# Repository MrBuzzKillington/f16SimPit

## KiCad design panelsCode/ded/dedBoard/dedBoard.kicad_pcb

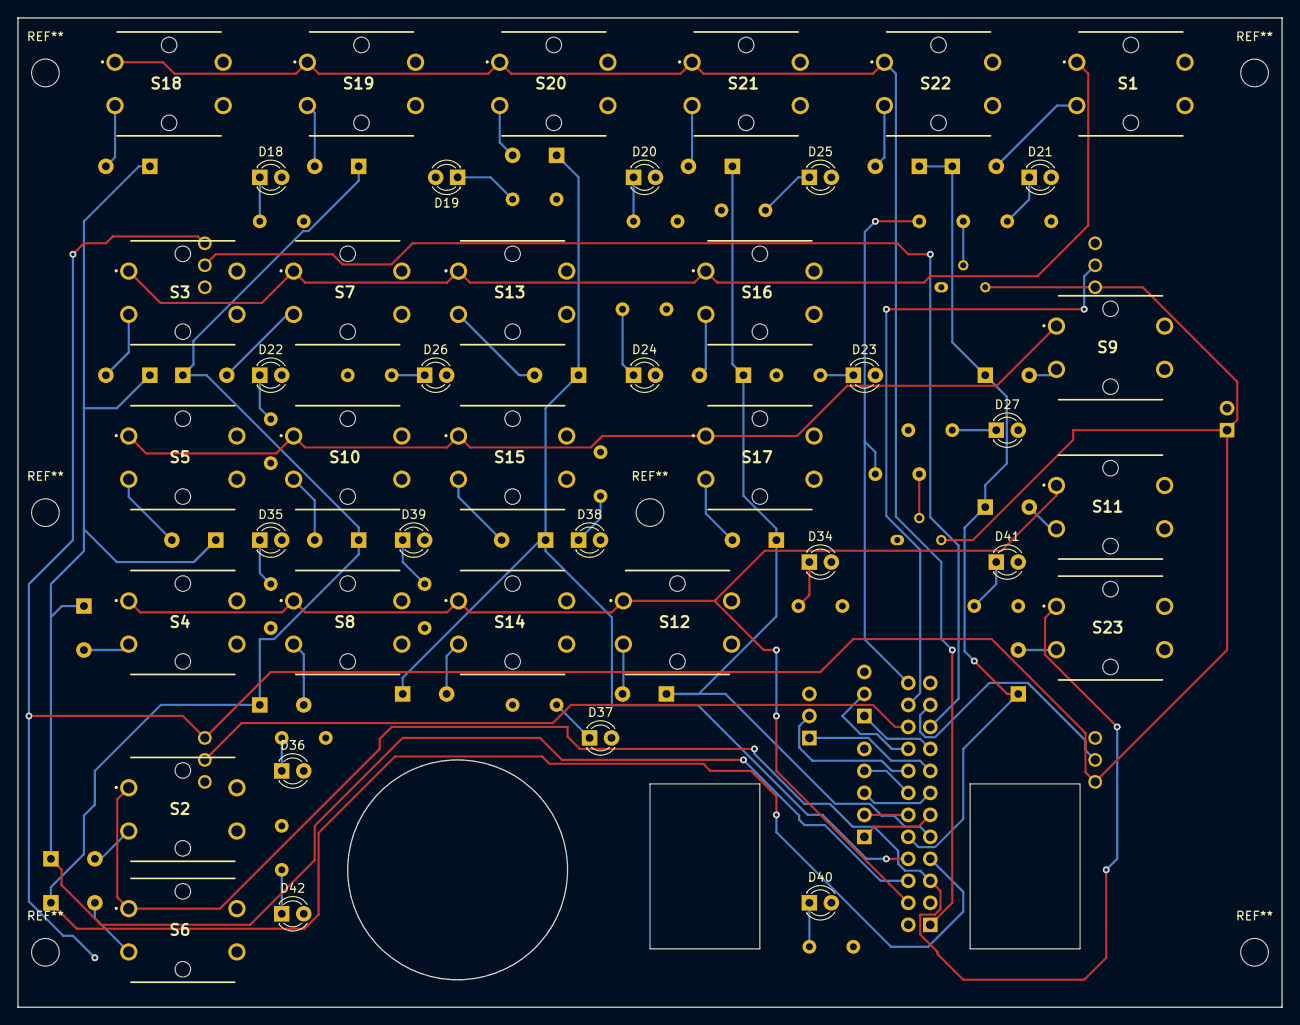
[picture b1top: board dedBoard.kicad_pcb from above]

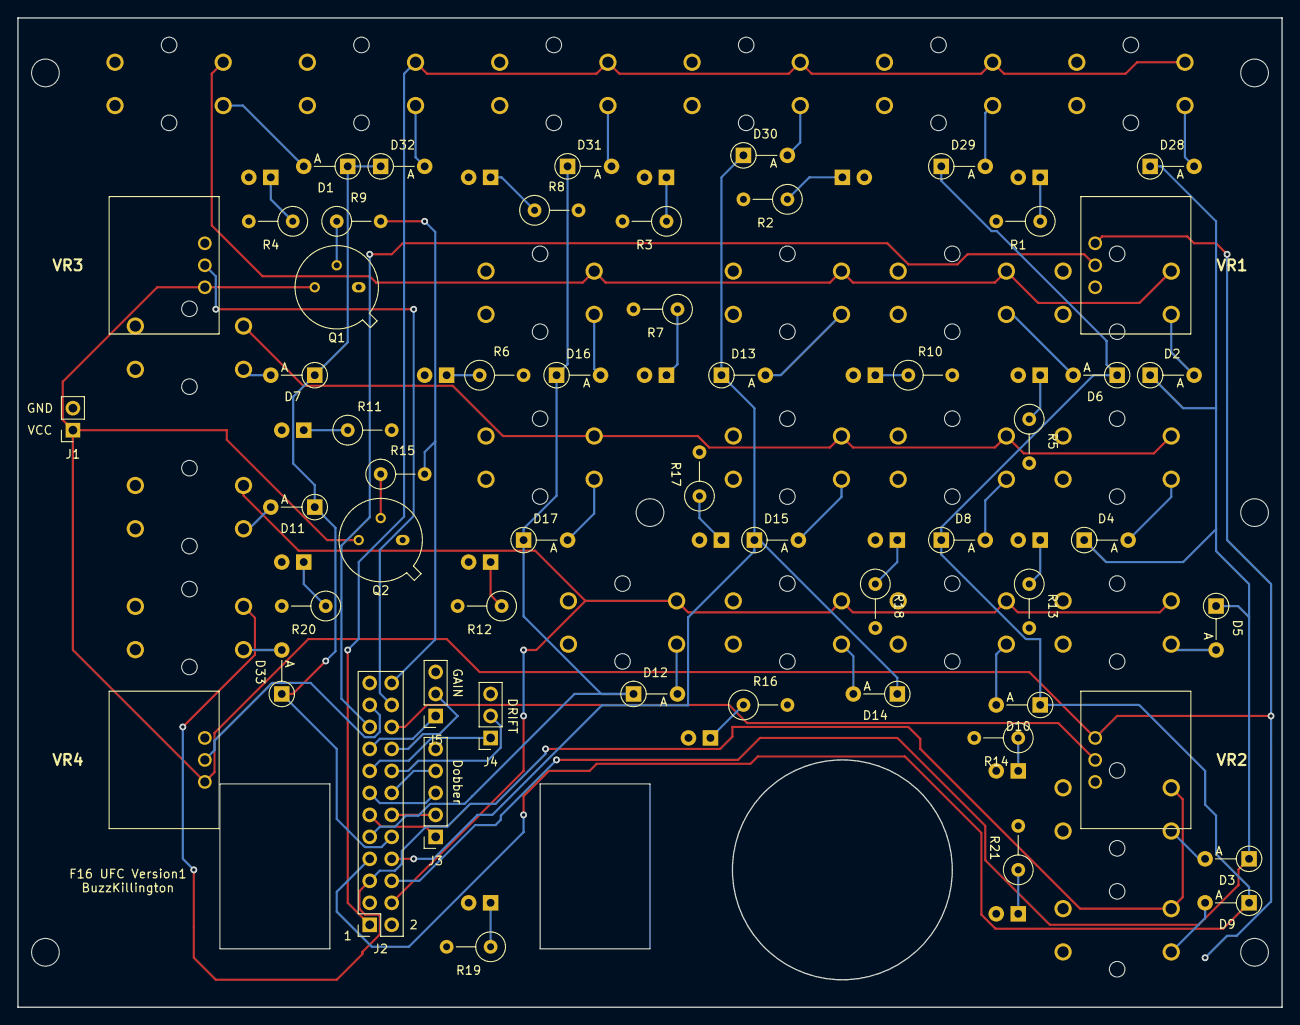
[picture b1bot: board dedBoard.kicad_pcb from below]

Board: 4 copper layers, 146.0 x 114.3 mm, 97 parts (55 on the bottom side), 71 nets.

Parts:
D1, D2, D3, D4, D5, D6, D7, D8, D9, D10, D11, D12, D13, D14, D15, D16, D17, D28, D29, D30, D31, D32, D33: D; D_A-405_P5.08mm_Vertical_AnodeUp
D18, D19, D20, D21, D22, D23, D24, D25, D26, D27, D34, D35, D36, D37, D38, D39, D40, D41, D42: LED; LED_D3.0mm
J1: Conn_01x02; PinSocket_1x02_P2.54mm_Vertical
J2: Conn_02x12_Odd_Even; PinSocket_2x12_P2.54mm_Vertical
J3: Conn_01x05; PinSocket_1x05_P2.54mm_Vertical
J4, J5: Conn_01x03; PinSocket_1x03_P2.54mm_Vertical
Q1, Q2: 2N2219; TO-39-3
R1, R2, R3, R4, R5, R6, R7, R8, R10, R11, R12, R13, R14, R16, R17, R18, R19, R20, R21: 520; R_Axial_DIN0309_L9.0mm_D3.2mm_P5.08mm_Vertical
R9, R15: 1000; R_Axial_DIN0309_L9.0mm_D3.2mm_P5.08mm_Vertical
S1, S2, S3, S4, S5, S6, S7, S8, S9, S10, S11, S12, S13, S14, S15, S16, S17, S18, S19, S20, S21, S22, S23: SKHCBEA010
VR1, VR2, VR3, VR4: 91A1A-B28-B13L; 91A1AB28B13L

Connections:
/LED1: D18.2, D19.2, D20.2, D21.2, D22.2, D23.2, D24.2, D25.2, D26.2, D27.2, Q1.1
/LED2: D34.2, D35.2, D36.2, D37.2, D38.2, D39.2, D40.2, D41.2, D42.2, Q2.1
COL1: D2.1, D3.1, D4.1, D5.1, D28.1, J2.6
COL2: D6.1, D8.1, D9.1, D10.1, D29.1, J2.7
COL3: D13.1, D14.1, D15.1, D30.1, J2.8
COL4: D12.1, D16.1, D17.1, D31.1, J2.9
COL5: D1.1, D7.1, D11.1, D32.1, D33.1, J2.10
GND: J1.2, J2.23, J3.5, J4.3, J5.3, R1.2, R2.2, R3.2, R4.2, R5.2, R6.2, R7.2, R8.2, R10.2, R11.2, R12.2, R13.2, R14.2, R16.2, R17.2, R18.2, R19.2, R20.2, R21.2, VR1.1, VR2.1, VR3.1, VR4.1
unnamed: D1.2, S1.3
unnamed: D2.2, S3.3
unnamed: D3.2, S2.3
unnamed: D4.2, S5.3
unnamed: D5.2, S4.3
unnamed: D6.2, S7.3
unnamed: D7.2, S9.3
unnamed: D8.2, S10.3
unnamed: D9.2, S6.3
unnamed: D10.2, S8.3
unnamed: D11.2, S11.3
unnamed: D12.2, S12.3
unnamed: D13.2, S13.3
unnamed: D14.2, S14.3
unnamed: D15.2, S15.3
unnamed: D16.2, S16.3
unnamed: D17.2, S17.3
unnamed: D18.1, R1.1
unnamed: D19.1, R2.1
unnamed: D20.1, R3.1
unnamed: D21.1, R4.1
unnamed: D22.1, R5.1
unnamed: D23.1, R6.1
unnamed: D24.1, R7.1
unnamed: D25.1, R8.1
unnamed: D26.1, R10.1
unnamed: D27.1, R11.1
unnamed: D28.2, S18.3
unnamed: D29.2, S19.3
unnamed: D30.2, S20.3
unnamed: D31.2, S21.3
unnamed: D32.2, S22.3
unnamed: D33.2, S23.3
unnamed: D34.1, R12.1
unnamed: D35.1, R13.1
unnamed: D36.1, R14.1
unnamed: D37.1, R16.1
unnamed: D38.1, R17.1
unnamed: D39.1, R18.1
unnamed: D40.1, R19.1
unnamed: D41.1, R20.1
unnamed: D42.1, R21.1
unnamed: Q1.2, R9.1
unnamed: Q2.2, R15.1
unnamed: S1.1, S3.1, S7.1, S13.1, S16.1
unnamed: S5.1, S9.1, S10.1, S15.1, S17.1
ROW1: J2.1, S18.1, S19.1, S20.1, S21.1, S22.1
ROW4: J2.4, S4.1, S8.1, S11.1, S12.1, S14.1
ROW5: J2.5, S2.1, S6.1, S23.1
VCC: J1.1, Q1.3, Q2.3, VR1.3, VR2.3, VR3.3, VR4.3
dobber1: J2.11, J3.1
dobber2: J2.12, J3.2
dobber3: J2.13, J3.3
dobber4: J2.14, J3.4
drift1: J2.15, J4.1
drift2: J2.16, J4.2
gain1: J2.17, J5.1
gain2: J2.18, J5.2
ledCtrl: J2.24, R9.2, R15.2
potBRT: J2.20, VR2.2
potCONT: J2.21, VR4.2
potDEPR: J2.22, VR3.2
potSym: J2.19, VR1.2

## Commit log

2022-06-05 Main push of all files except the dcsBios arudino code
2022-09-25 Added Panel source code
2022-09-25 gauge cluster
2022-09-26 added panels TEst
2022-10-06 fix to warning lights
2022-10-06 Updates for oh shit lights and master caution
2022-10-07 addecd self test
2022-10-07 slowed gauge
2022-10-09 added aoa panel
2022-10-10 added aruduino step
2022-10-18 fixes to panels and new code for ecm
2022-10-21 added fixes to engine gauges and created library to f x168 driven by easydriver chip
2022-12-29 added proper stepper control to fuel gauge
2022-12-31 added canopy ejection
2023-03-20 added self test to flight control panel to cycle the backlight
2023-03-26 added firstCaptureModule
2023-03-26 Added screen clone node
2023-03-26 removed code
2023-05-06 light fixes
2023-07-06 changes to throttle arm for new arm
2023-10-01 fixed stor jet
2023-12-26 fix for ecm panel sync logic
